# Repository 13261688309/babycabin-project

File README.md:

# 智能婴儿陪护舱 BabyCabin

大学生创新训练项目结题成果。系统由 STM32H743、ESP32 图传、CI1302 离线语音、DHT11、电脑端网页以及鸿蒙 APP 组成。当前交付是无人桌面演示原型，不用于婴儿或载人，不是医疗或监护设备。

| 成果 | 位置 |
| --- | --- |
| STM32H743 CubeIDE 工程与 F407 早期工程 | [H743](fetal-baby/) / [F407](firmware-f407/) |
| GB01 台架快照、语音控制候选及模块源码 | [firmware-snapshots](firmware-snapshots/) / [firmware-candidates](firmware-candidates/) |
| 四层 KiCad 原理图、PCB、封装库及询价材料 | [hardware](hardware/) |
| 专用语音词表、模型训练与验证材料 | [voice](voice/) / [vision](vision/) |
| 电脑端网页、摄像头与识别服务 | [babycabin-desktop-web](https://github.com/13261688309/babycabin-desktop-web) |
| 鸿蒙 APP | [babycabin-harmony-app](https://github.com/13261688309/babycabin-harmony-app) |

## 复现与边界

- STM32CubeIDE 导入对应目录下的工程，保留原第三方组件许可证。GB01 台架快照和语音候选不是同一个固件；候选构建记录不能替代整机上板或运动验收。
- 四层板为设计与询价版本，Gerber、BOM、贴片坐标只供报价核对，不代表制造批准、装配确认或电气验收。
- 电脑端运行视觉推理，ESP32 提供画面，STM32 和手机端处理各自的状态或操作。Cry 等类别是图像信号，不是诊断；模型对照的开发集不是独立实机准确率评估。
- 不包含原始训练影像、现场串口日志、整片 Flash 备份、账号配置、配网密钥或厂商原始工具包。外部摄像头的厂商固件不在项目源码内。

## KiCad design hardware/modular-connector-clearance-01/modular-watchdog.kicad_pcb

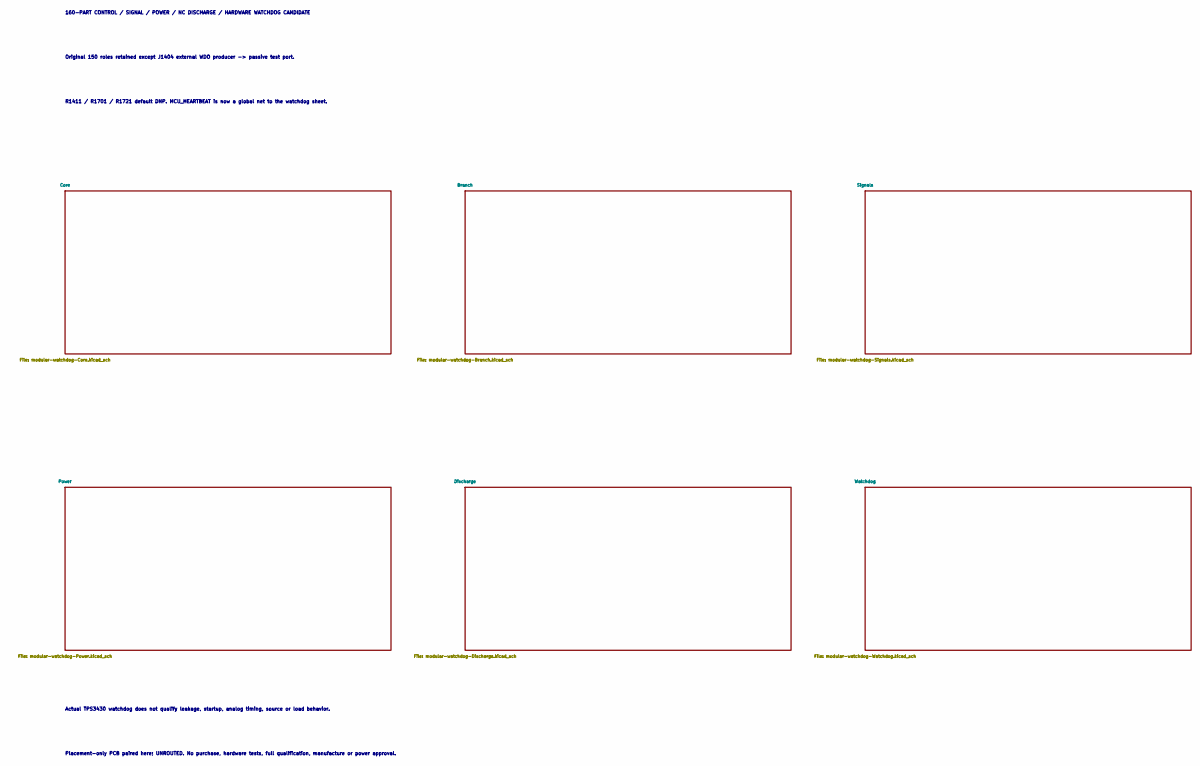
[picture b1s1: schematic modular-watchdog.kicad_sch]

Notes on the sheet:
160-PART CONTROL / SIGNAL / POWER / NC DISCHARGE / HARDWARE WATCHDOG CANDIDATE
Original 150 roles retained except J1404 external WDO producer -> passive test port.
R1411 / R1701 / R1721 default DNP. MCU_HEARTBEAT is now a global net to the watchdog sheet.
Actual TPS3430 watchdog does not qualify leakage, startup, analog timing, source or load behavior.
Placement-only PCB paired here; UNROUTED. No purchase, hardware tests, full qualification, manufacture or power approval.

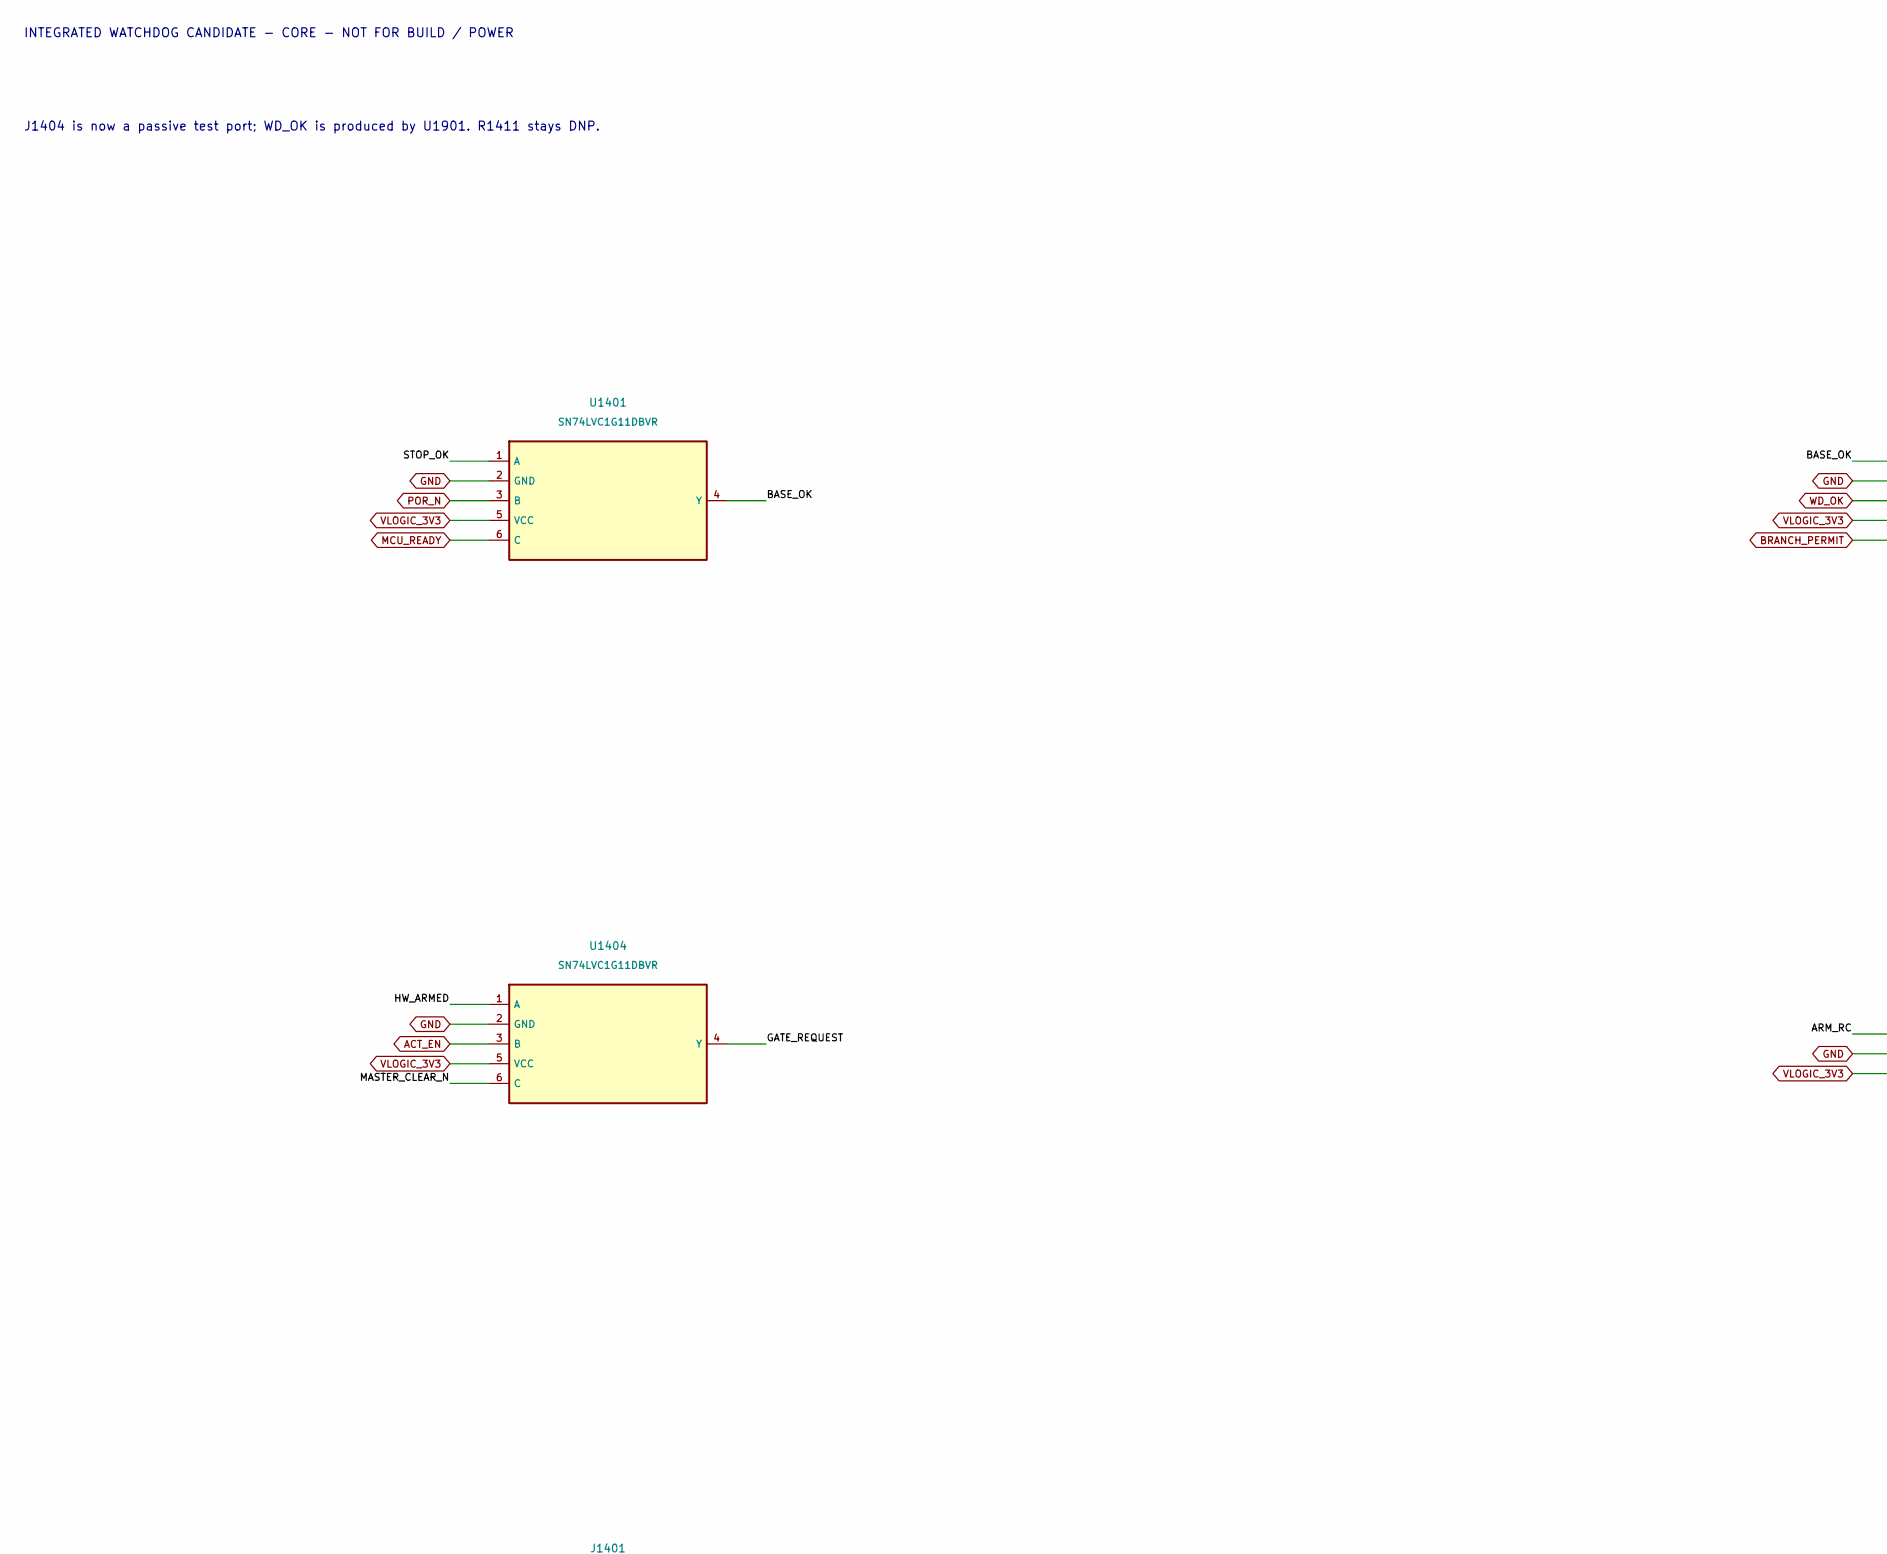
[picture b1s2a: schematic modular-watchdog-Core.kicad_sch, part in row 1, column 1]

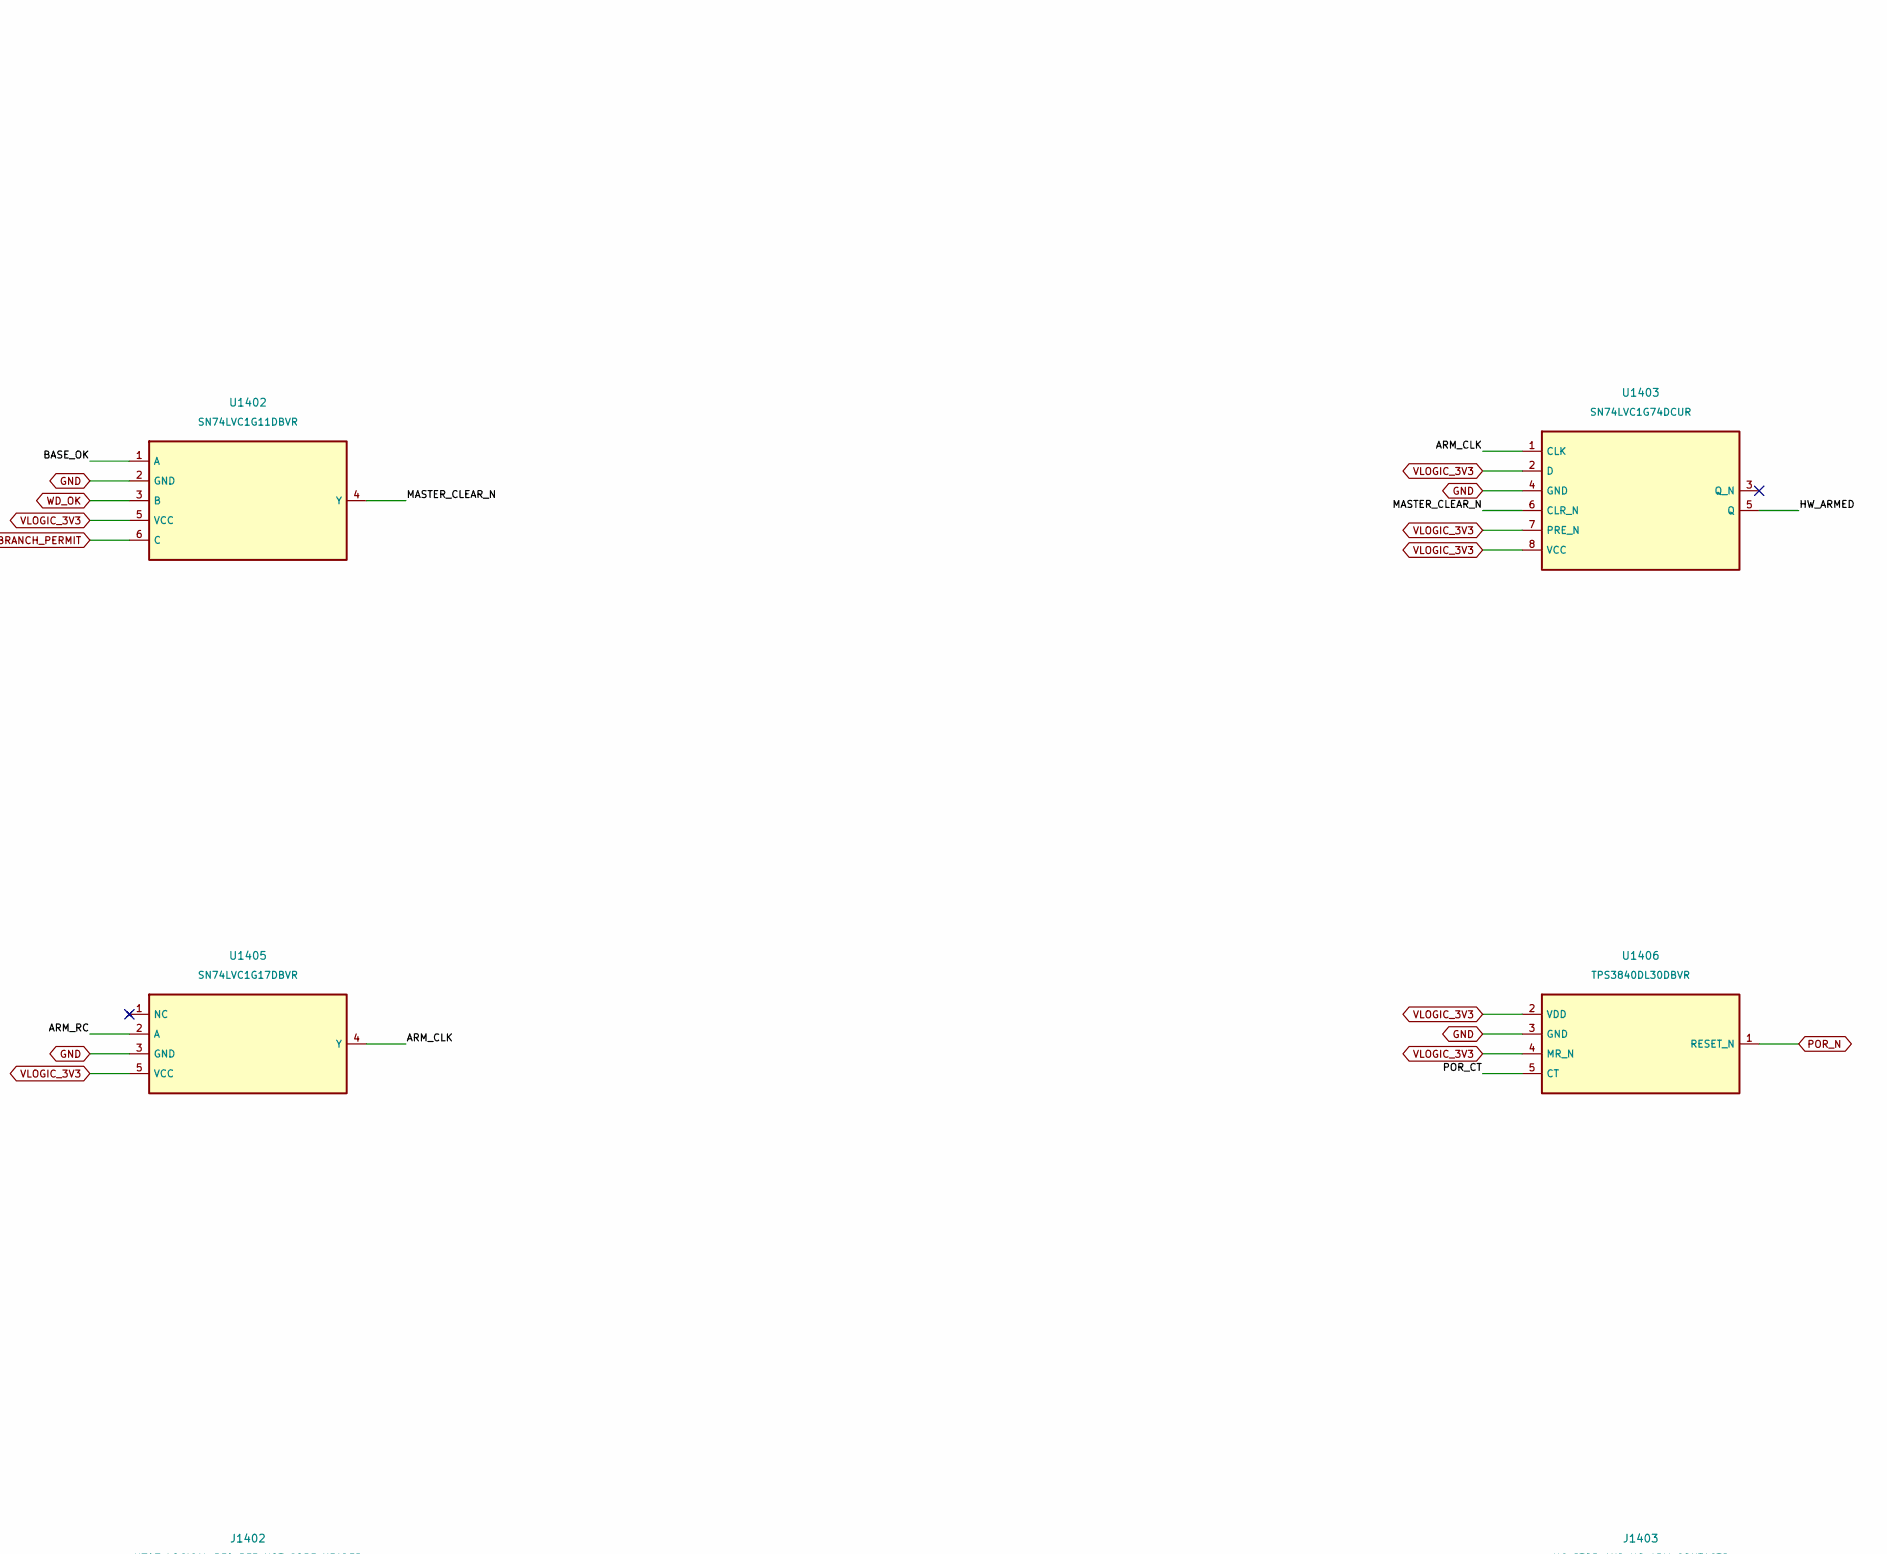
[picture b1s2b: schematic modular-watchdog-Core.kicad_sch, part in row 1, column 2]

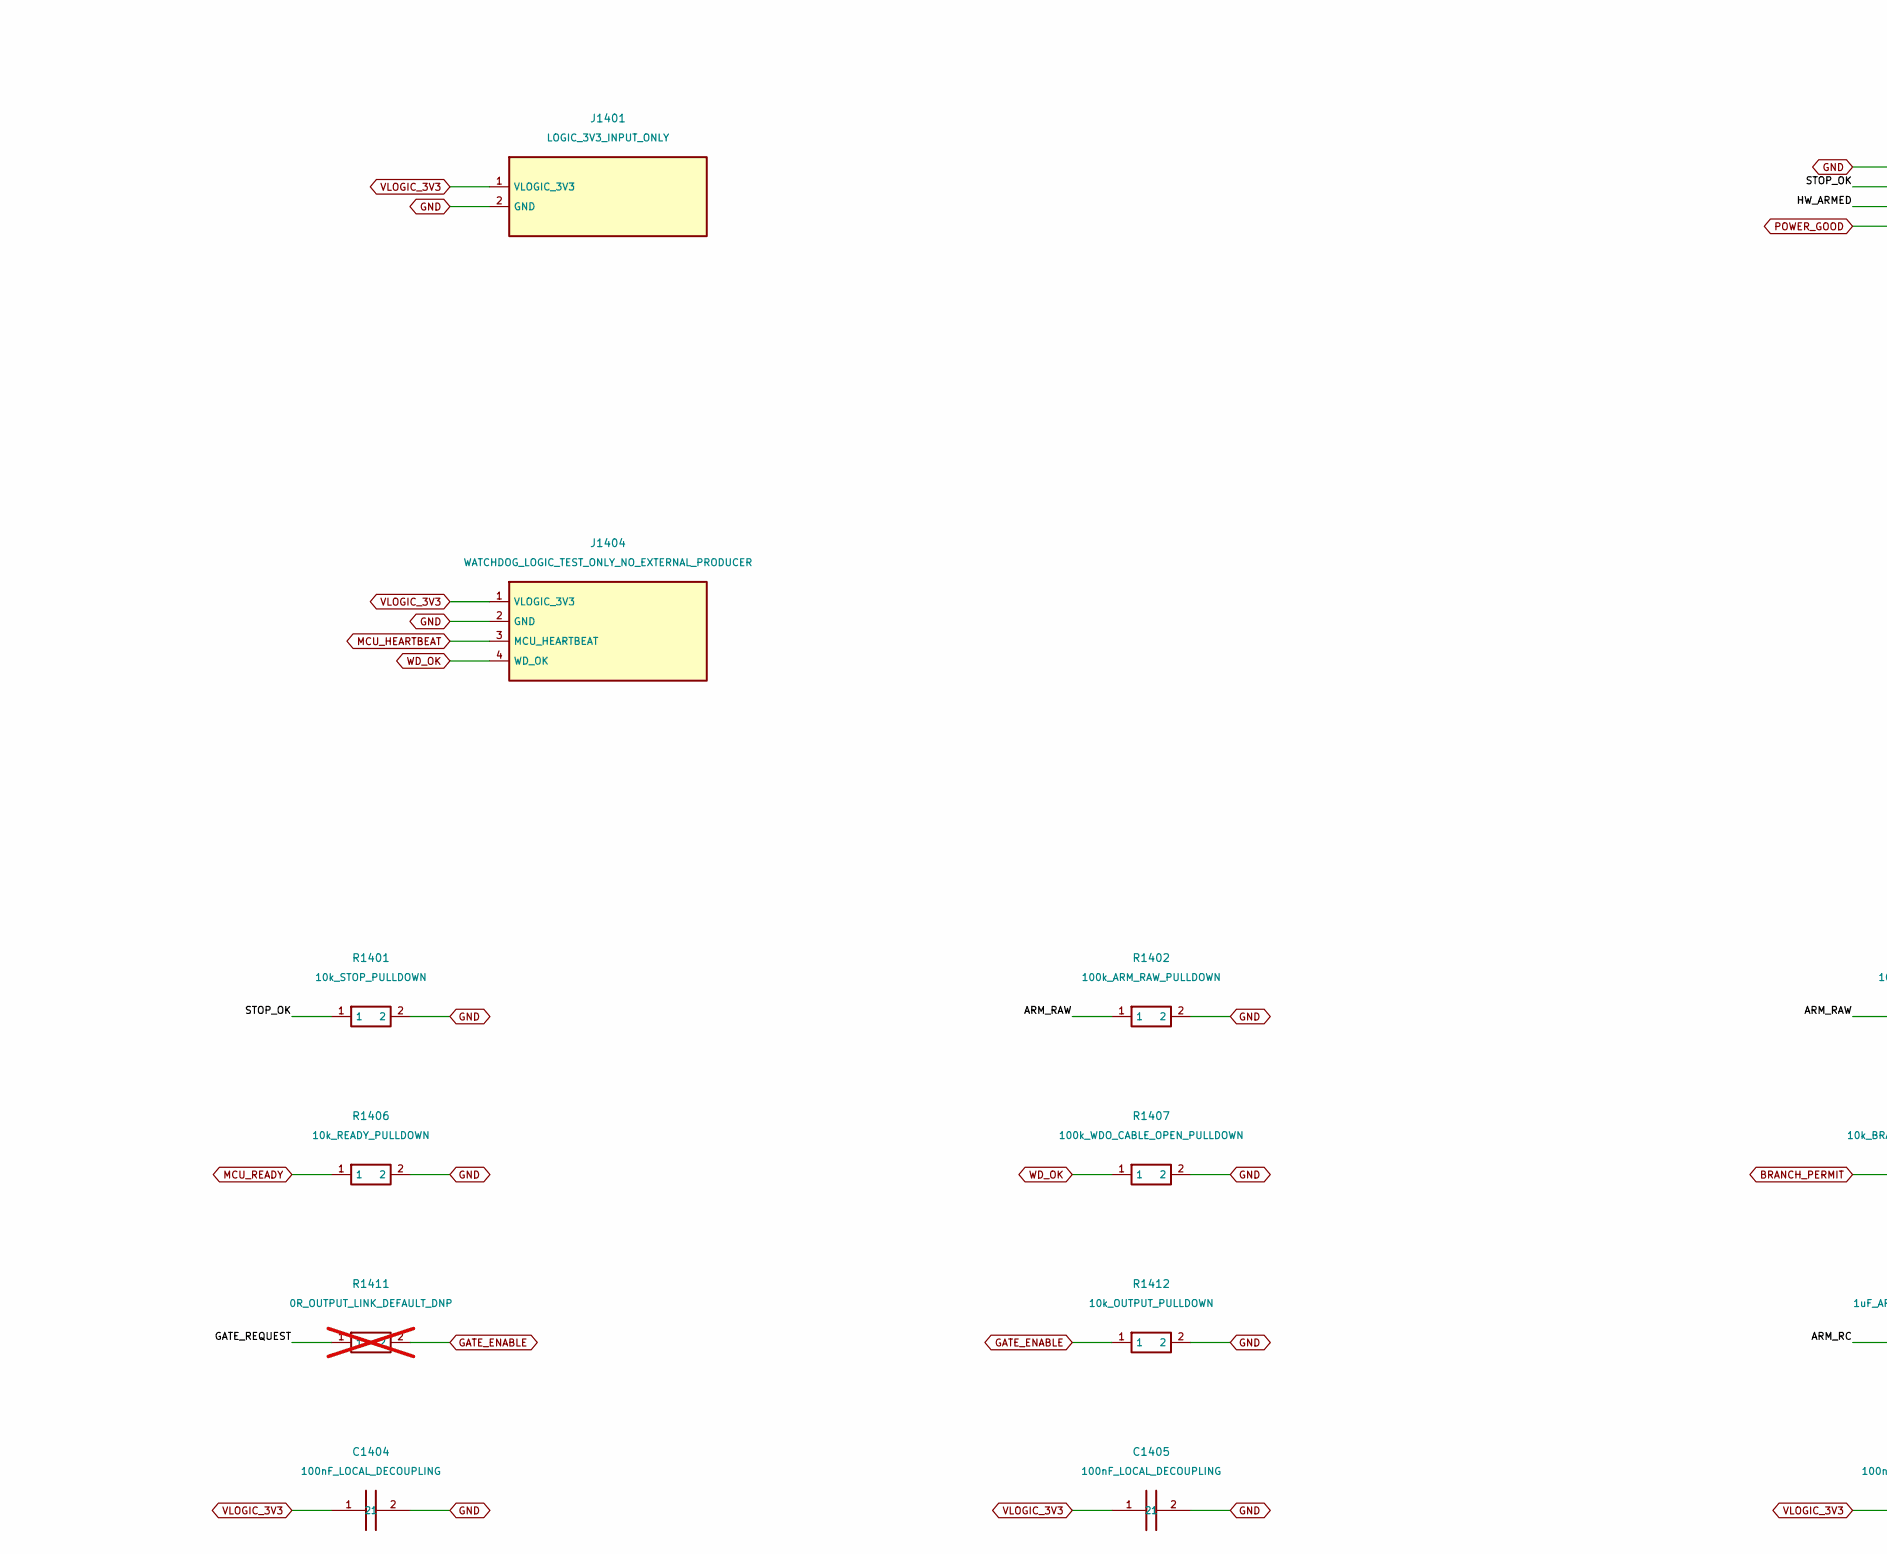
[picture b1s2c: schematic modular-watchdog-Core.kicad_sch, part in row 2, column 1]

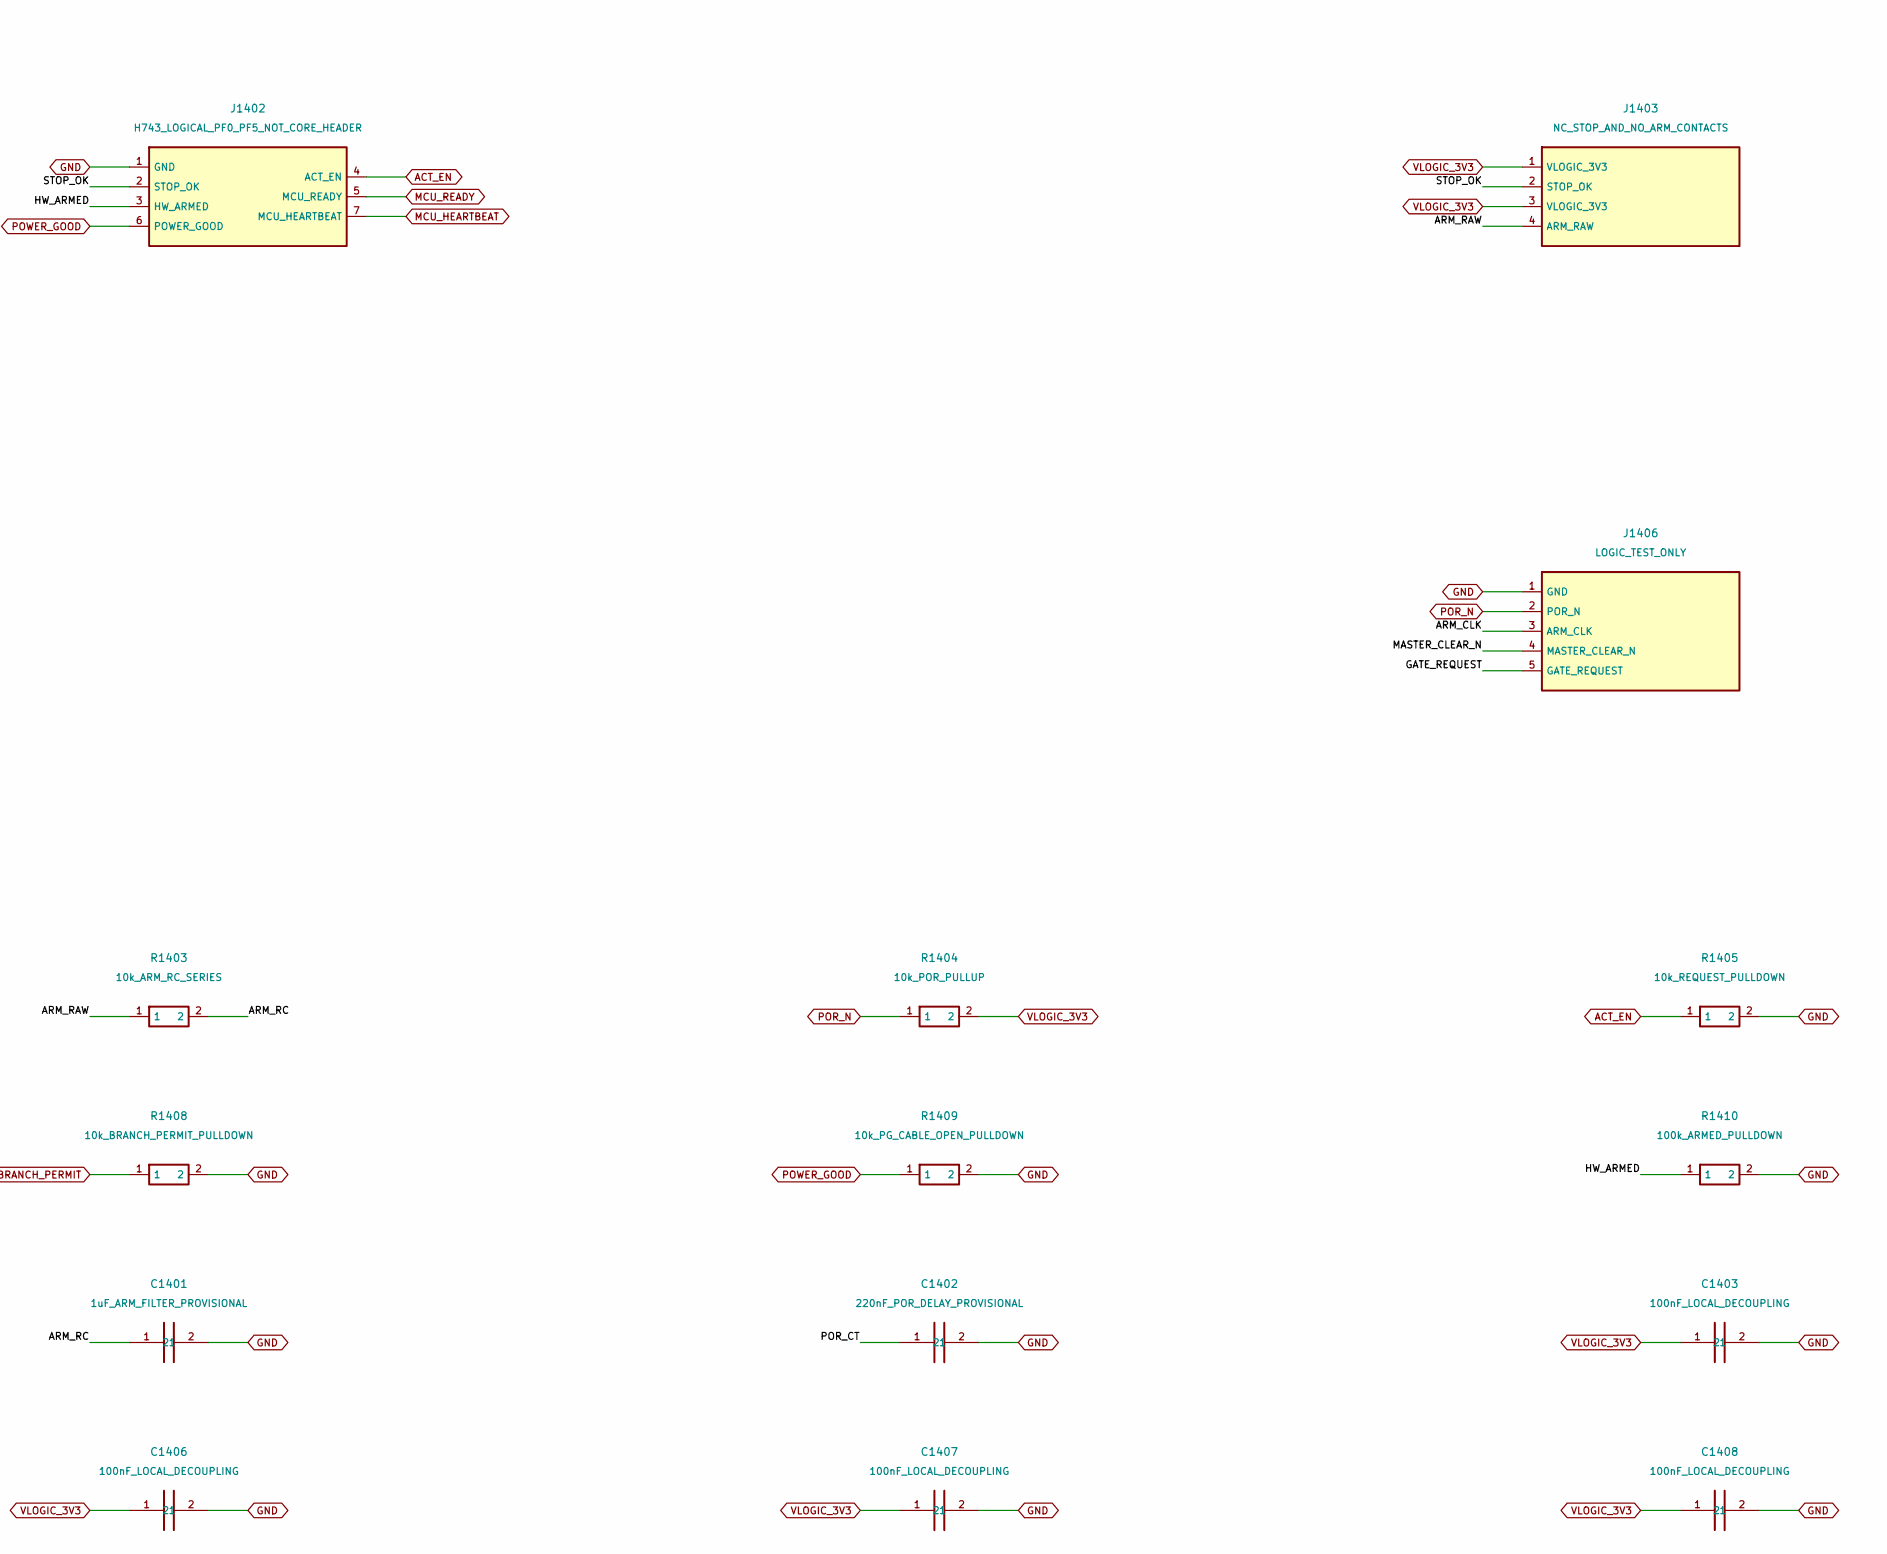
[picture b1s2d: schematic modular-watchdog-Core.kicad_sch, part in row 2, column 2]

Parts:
C1401: 1uF_ARM_FILTER_PROVISIONAL; TDK_1206_Reflow_CapacitorDraft
C1402: 220nF_POR_DELAY_PROVISIONAL; TDK_0805_Reflow_CapacitorDraft
C1403, C1404, C1405, C1406, C1407, C1408: 100nF_LOCAL_DECOUPLING; TDK_0603_Reflow_CapacitorDraft
J1401: LOGIC_3V3_INPUT_ONLY; JST_XH_B2B-XH-A_1x02_P2.50mm_Vertical_ConnectorDraft
J1402: H743_LOGICAL_PF0_PF5_NOT_CORE_HEADER; JST_XH_B7B-XH-A_1x07_P2.50mm_Vertical_ConnectorDraft
J1403: NC_STOP_AND_NO_ARM_CONTACTS; JST_PH_B4B-PH-K_1x04_P2.00mm_Vertical_ConnectorDraft
J1404: WATCHDOG_LOGIC_TEST_ONLY_NO_EXTERNAL_PRODUCER; JST_XH_B4B-XH-A_1x04_P2.50mm_Vertical_ConnectorDraft
J1406: LOGIC_TEST_ONLY; JST_XH_B5B-XH-A_1x05_P2.50mm_Vertical_ConnectorDraft
R1401: 10k_STOP_PULLDOWN; Vishay_CRCW0805_Reflow_ResistorDraft
R1402: 100k_ARM_RAW_PULLDOWN; Vishay_CRCW0805_Reflow_ResistorDraft
R1403: 10k_ARM_RC_SERIES; Vishay_CRCW0805_Reflow_ResistorDraft
R1404: 10k_POR_PULLUP; Vishay_CRCW0805_Reflow_ResistorDraft
R1405: 10k_REQUEST_PULLDOWN; Vishay_CRCW0805_Reflow_ResistorDraft
R1406: 10k_READY_PULLDOWN; Vishay_CRCW0805_Reflow_ResistorDraft
R1407: 100k_WDO_CABLE_OPEN_PULLDOWN; Vishay_CRCW0805_Reflow_ResistorDraft
R1408: 10k_BRANCH_PERMIT_PULLDOWN; Vishay_CRCW0805_Reflow_ResistorDraft
R1409: 10k_PG_CABLE_OPEN_PULLDOWN; Vishay_CRCW0805_Reflow_ResistorDraft
R1410: 100k_ARMED_PULLDOWN; Vishay_CRCW0805_Reflow_ResistorDraft
R1411: 0R_OUTPUT_LINK_DEFAULT_DNP; Vishay_CRCW0805_Reflow_ResistorDraft; not fitted
R1412: 10k_OUTPUT_PULLDOWN; Vishay_CRCW0805_Reflow_ResistorDraft
U1401, U1402, U1404: SN74LVC1G11DBVR; TI_DBV0006A_ModularLogicDraft
U1403: SN74LVC1G74DCUR; TI_DCU0008A_ModularLogicDraft
U1405: SN74LVC1G17DBVR; TI_DBV0005A_ModularLogicDraft
U1406: TPS3840DL30DBVR; TI_DBV0005A_ModularLogicDraft

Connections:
/Core/ARM_CLK: J1406.3 (ARM_CLK), U1403.1 (CLK), U1405.4 (Y)
/Core/ARM_RAW: J1403.4 (ARM_RAW), R1402.1, R1403.1
/Core/ARM_RC: C1401.1, R1403.2, U1405.2 (A)
/Core/BASE_OK: U1401.4 (Y), U1402.1 (A)
/Core/GATE_REQUEST: J1406.5 (GATE_REQUEST), R1411.1, U1404.4 (Y)
/Core/HW_ARMED: J1402.3 (HW_ARMED), R1410.1, U1403.5 (Q), U1404.1 (A)
/Core/MASTER_CLEAR_N: J1406.4 (MASTER_CLEAR_N), U1402.4 (Y), U1403.6 (CLR_N), U1404.6 (C)
/Core/POR_CT: C1402.1, U1406.5 (CT)
/Core/STOP_OK: J1402.2 (STOP_OK), J1403.2 (STOP_OK), R1401.1, U1401.1 (A)
ACT_EN: J1402.4 (ACT_EN), R1405.1, U1404.3 (B); also elsewhere on the board
BRANCH_PERMIT: R1408.1, U1402.6 (C); also elsewhere on the board
GATE_ENABLE: R1411.2, R1412.1; also elsewhere on the board
GND: C1401.2, C1402.2, C1403.2, C1404.2, C1405.2, C1406.2, C1407.2, C1408.2, J1401.2 (GND), J1402.1 (GND), J1404.2 (GND), J1406.1 (GND), R1401.2, R1402.2, R1405.2, R1406.2, R1407.2, R1408.2, R1409.2, R1410.2, R1412.2, U1401.2 (GND), U1402.2 (GND), U1403.4 (GND), U1404.2 (GND), U1405.3 (GND), U1406.3 (GND); also elsewhere on the board
MCU_HEARTBEAT: J1402.7 (MCU_HEARTBEAT), J1404.3 (MCU_HEARTBEAT); also elsewhere on the board
MCU_READY: J1402.5 (MCU_READY), R1406.1, U1401.6 (C); also elsewhere on the board
POR_N: J1406.2 (POR_N), R1404.1, U1401.3 (B), U1406.1 (RESET_N); also elsewhere on the board
POWER_GOOD: J1402.6 (POWER_GOOD), R1409.1; also elsewhere on the board
VLOGIC_3V3: C1403.1, C1404.1, C1405.1, C1406.1, C1407.1, C1408.1, J1401.1 (VLOGIC_3V3), J1403.1 (VLOGIC_3V3), J1403.3 (VLOGIC_3V3), J1404.1 (VLOGIC_3V3), R1404.2, U1401.5 (VCC), U1402.5 (VCC), U1403.2 (D), U1403.7 (PRE_N), U1403.8 (VCC), U1404.5 (VCC), U1405.5 (VCC), U1406.2 (VDD), U1406.4 (MR_N); also elsewhere on the board
WD_OK: J1404.4 (WD_OK), R1407.1, U1402.3 (B); also elsewhere on the board

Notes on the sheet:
INTEGRATED WATCHDOG CANDIDATE - CORE - NOT FOR BUILD / POWER
J1404 is now a passive test port; WD_OK is produced by U1901. R1411 stays DNP.

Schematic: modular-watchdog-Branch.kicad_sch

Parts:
C1501, C1502, C1504, C1505, C1506, C1507, C1508, C1509: 100nF_LOCAL_DECOUPLING; TDK_0603_Reflow_CapacitorDraft
C1503: 100nF_LOCAL_DECOUPLING; TDK_0603_Reflow_CapacitorDraft_AssemblyMarker
D201, D202, D203, D204: BAV199,215; Nexperia_BAV199_SOT23_DiscreteDraft
J1501: VOLTAGE_SENSE_ONLY_POSITIVE_ENVELOPE_REQUIRED; JST_PH_B5B-PH-K_1x05_P2.00mm_Vertical_ConnectorDraft
J1502: POWER_STAGE_LOGIC_TEST_ONLY; JST_PH_B7B-PH-K_1x07_P2.00mm_Vertical_ConnectorDraft
R9, R23: 82k_1pct_REVIEW; Vishay_CRCW0805_Reflow_ResistorDraft_AssemblyMarker
R10, R24: 10k_1pct_REVIEW; Vishay_CRCW0805_Reflow_ResistorDraft_AssemblyMarker
R11: 107k_0p1pct_MOTOR_RAIL_UV; Vishay_TNPW0805_Reflow_ResistorDraft_AssemblyMarker
R12, R26: 10k_0p1pct_RAIL_DIVIDER; Vishay_TNPW0805_Reflow_ResistorDraft_AssemblyMarker
R13, R14, R27, R28, R31: 10k; Vishay_CRCW0805_Reflow_ResistorDraft
R25: 115k_0p1pct_SERVO_RAIL_UV; Vishay_TNPW0805_Reflow_ResistorDraft_AssemblyMarker
R29: 100k_1pct_REVIEW; Vishay_CRCW0805_Reflow_ResistorDraft_AssemblyMarker
R201, R202: 1M_1pct_REVIEW; Vishay_CRCW0805_Reflow_ResistorDraft
U8, U9: TPS3700DDCR; TI_DDC0006A_ModularLogicDraft
U27: TPS3808G01DBVR; TI_DBV0006A_ModularLogicDraft
U800: SN74LVC04ADR; TI_D0014A_ModularLogicDraft
U801, U802: SN74LVC08ADR; TI_D0014A_ModularLogicDraft
U804, U805: SN74LVC11ADR; TI_D0014A_ModularLogicDraft
U806: SN74LVC32ADR; TI_D0014A_ModularLogicDraft

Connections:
/Branch/FAULT_REQUEST: U806.5 (2B), U806.11 (4Y)
/Branch/FAULT_RESET_N: U801.9 (3A), U801.11 (4Y)
/Branch/FAULT_SET: U801.10 (3B), U806.6 (2Y)
/Branch/M_BIAS_ANODE: D202.1 (A1), R201.2
/Branch/M_OUT_BAD: R14.2, U8.6 (OUTB), U800.5 (3A)
/Branch/M_OUT_OK: U800.6 (3Y), U802.5 (2B)
/Branch/M_OUT_SENSE: R11.2, R12.1, U8.4 (INB-)
/Branch/M_PG_VALID: J1502.4 (M_PG_VALID), U801.1 (1A), U802.6 (2Y), U804.2 (1B)
/Branch/M_SRC_OK: R13.2, U8.1 (OUTA), U802.4 (2A), U805.9 (3A)
/Branch/M_VIN_ISO: D201.2 (K2), D201.3 (K1_A2), D202.2 (K2), D202.3 (K1_A2), R9.1
/Branch/M_VIN_SENSE: R9.2, R10.1, U8.3 (INA+)
/Branch/POWER_BAD: U800.2 (1Y), U804.5 (2C)
/Branch/POWER_FAULT: J1502.6 (POWER_FAULT), U800.3 (2A), U801.8 (3Y), U806.4 (2A)
/Branch/POWER_FAULT_N: U800.4 (2Y), U804.10 (3B), U805.2 (1B), U805.11 (3C)
/Branch/POWER_NOT_SEEN: U800.10 (5Y), U805.5 (2C)
/Branch/POWER_SEEN: U800.11 (5A), U801.6 (2Y), U804.3 (2A), U806.1 (1A)
/Branch/POWER_TRIP: U804.6 (2Y), U806.9 (3A)
/Branch/RAIL_TRIP: U806.8 (3Y), U806.12 (4A)
/Branch/SEEN_SET: U801.5 (2B), U806.3 (1Y)
/Branch/SIGNAL_EN_RAW: U804.9 (3A), U804.12 (1Y)
/Branch/STARTUP_TRIP: U805.6 (2Y), U806.10 (3B)
/Branch/START_CT: R29.2, U27.4 (CT)
/Branch/START_EXPIRED: J1502.7 (START_EXPIRED), R31.2, U27.1 (~RESET), U805.4 (2B)
/Branch/S_BIAS_ANODE: D204.1 (A1), R202.2
/Branch/S_OUT_BAD: R28.2, U9.6 (OUTB), U800.9 (4A)
/Branch/S_OUT_OK: U800.8 (4Y), U802.10 (3B)
/Branch/S_OUT_SENSE: R25.2, R26.1, U9.4 (INB-)
/Branch/S_PG_VALID: J1502.5 (S_PG_VALID), U801.2 (1B), U802.8 (3Y), U804.13 (1C)
/Branch/S_SRC_OK: R27.2, U9.1 (OUTA), U802.9 (3A), U805.10 (3B)
/Branch/S_VIN_ISO: D203.2 (K2), D203.3 (K1_A2), D204.2 (K2), D204.3 (K1_A2), R23.1
/Branch/S_VIN_SENSE: R23.2, R24.1, U9.3 (INA+)
/Branch/WD_BAD: U800.12 (6Y), U802.13 (4B)
/Branch/WD_TRIP: U802.11 (4Y), U806.13 (4B)
ACT_EN: U27.5 (SENSE), U801.4 (2A), U802.12 (4A), U804.4 (2B), U805.3 (2A); also elsewhere on the board
BRANCH_PERMIT: U805.8 (3Y); also elsewhere on the board
GATE_ENABLE: U804.1 (1A), U805.1 (1A); also elsewhere on the board
GND: C1501.2, C1502.2, C1503.2, C1504.2, C1505.2, C1506.2, C1507.2, C1508.2, C1509.2, J1501.1 (GND), J1502.1 (GND), R10.2, R12.2, R24.2, R26.2, U8.2 (GND), U9.2 (GND), U27.2 (GND), U800.7 (GND), U801.7 (GND), U802.1 (1A), U802.2 (1B), U802.7 (GND), U804.7 (GND), U805.7 (GND), U806.7 (GND); also elsewhere on the board
LOAD_RAILS_GOOD: U801.3 (1Y); also elsewhere on the board
MCU_READY: U801.13 (4B); also elsewhere on the board
M_VIN: D201.1 (A1), J1501.2 (M_VIN); also elsewhere on the board
M_VOUT: J1501.4 (M_VOUT), R11.1; also elsewhere on the board
POR_N: U27.3 (~MR), U801.12 (4A); also elsewhere on the board
POWER_EN: J1502.2 (POWER_EN), U805.12 (1Y); also elsewhere on the board
POWER_GOOD: U800.1 (1A), U806.2 (1B); also elsewhere on the board
SIGNAL_EN_PRE: J1502.3 (SIGNAL_EN_PRE), U804.8 (3Y); also elsewhere on the board
S_VIN: D203.1 (A1), J1501.3 (S_VIN); also elsewhere on the board
S_VOUT: J1501.5 (S_VOUT), R25.1; also elsewhere on the board
VLOGIC_3V3: C1501.1, C1502.1, C1503.1, C1504.1, C1505.1, C1506.1, C1507.1, C1508.1, C1509.1, R13.1, R14.1, R27.1, R28.1, R29.1, R31.1, R201.1, R202.1, U8.5 (VDD), U9.5 (VDD), U27.6 (VDD), U800.14 (VCC), U801.14 (VCC), U802.14 (VCC), U804.14 (VCC), U805.14 (VCC), U806.14 (VCC); also elsewhere on the board
WD_OK: U800.13 (6A), U804.11 (3C), U805.13 (1C); also elsewhere on the board

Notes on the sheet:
INTEGRATED WATCHDOG CANDIDATE - BRANCH - NOT FOR BUILD / POWER
Existing voltage monitors / fault memory retained. No transient or timing qualification.
